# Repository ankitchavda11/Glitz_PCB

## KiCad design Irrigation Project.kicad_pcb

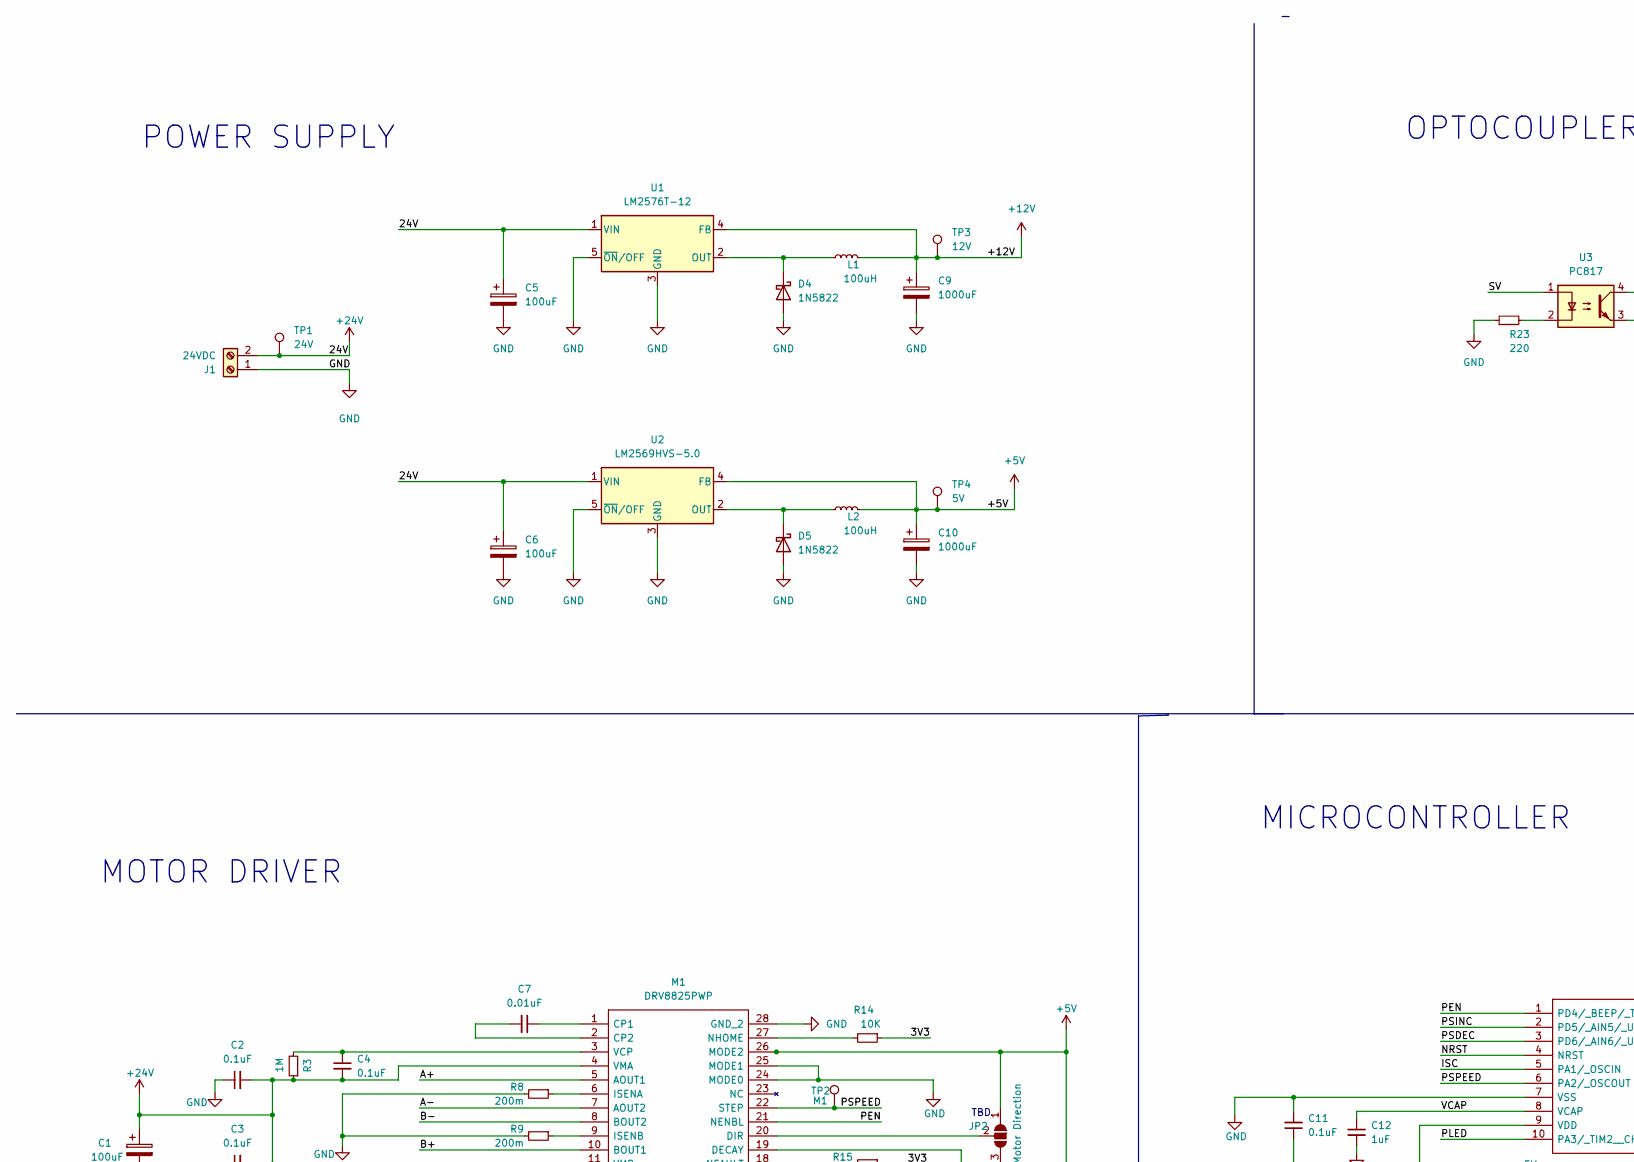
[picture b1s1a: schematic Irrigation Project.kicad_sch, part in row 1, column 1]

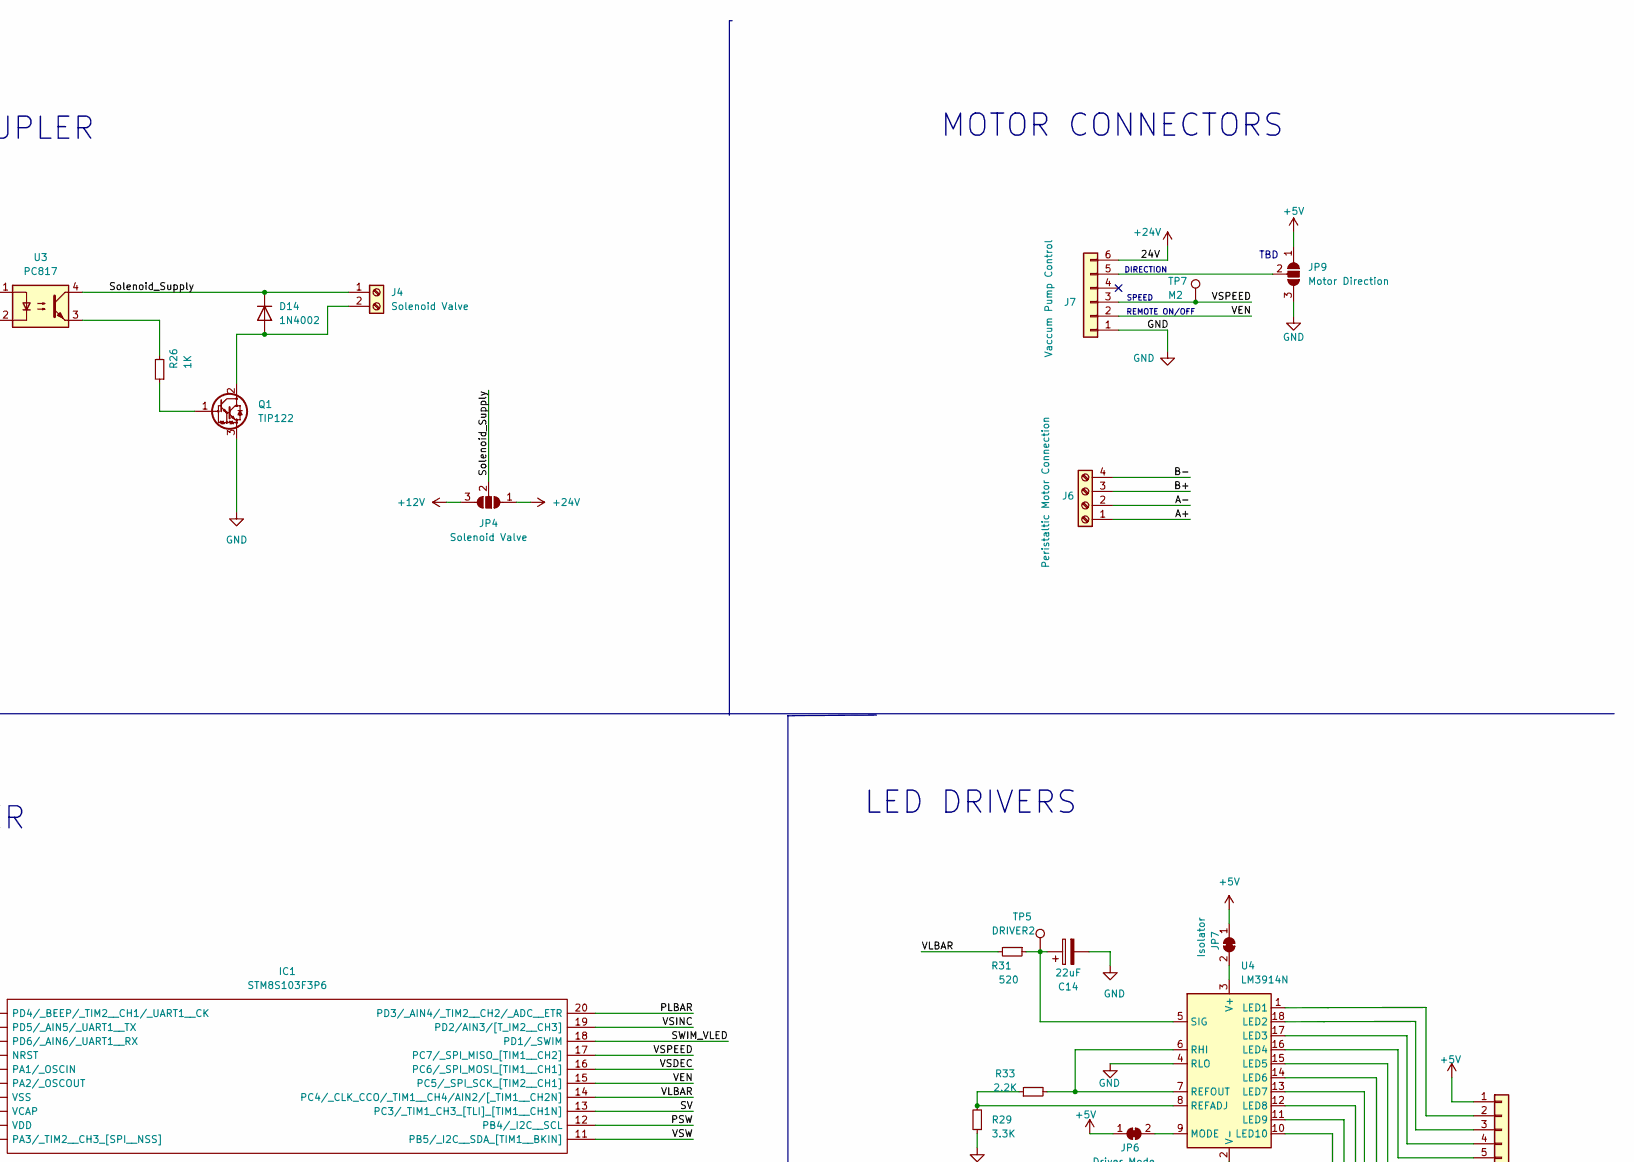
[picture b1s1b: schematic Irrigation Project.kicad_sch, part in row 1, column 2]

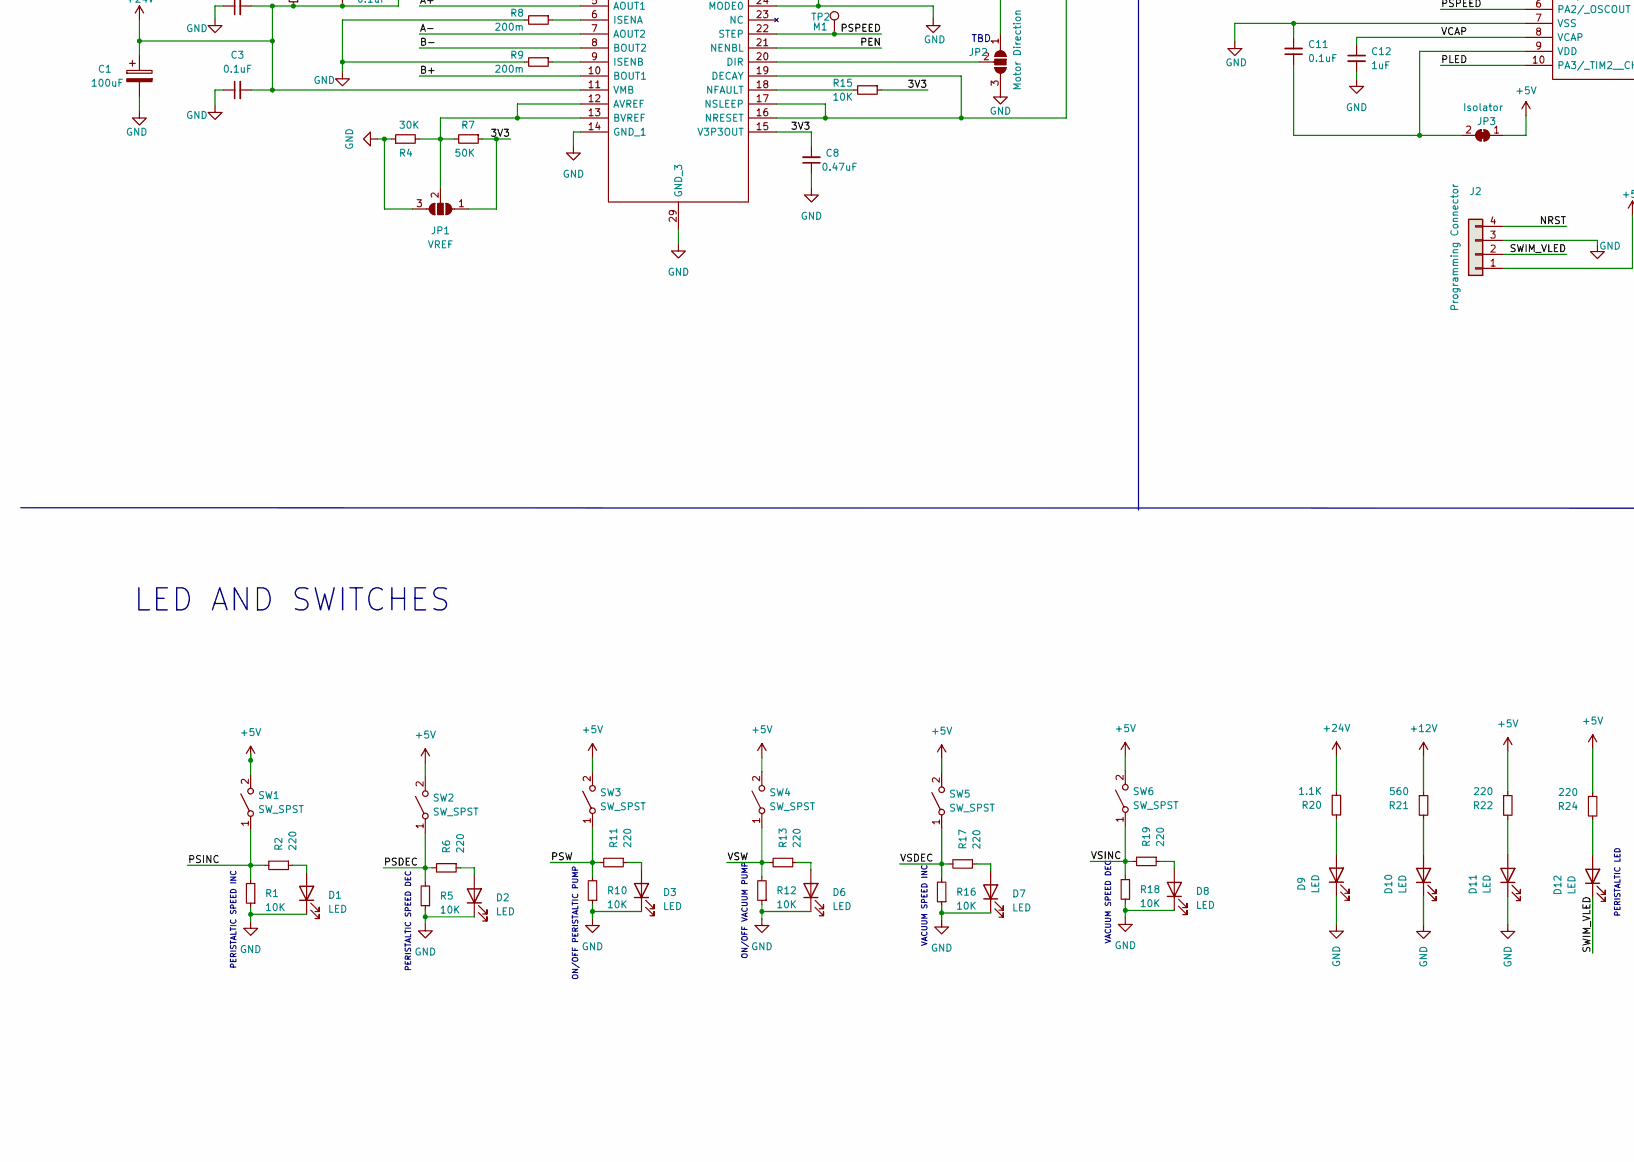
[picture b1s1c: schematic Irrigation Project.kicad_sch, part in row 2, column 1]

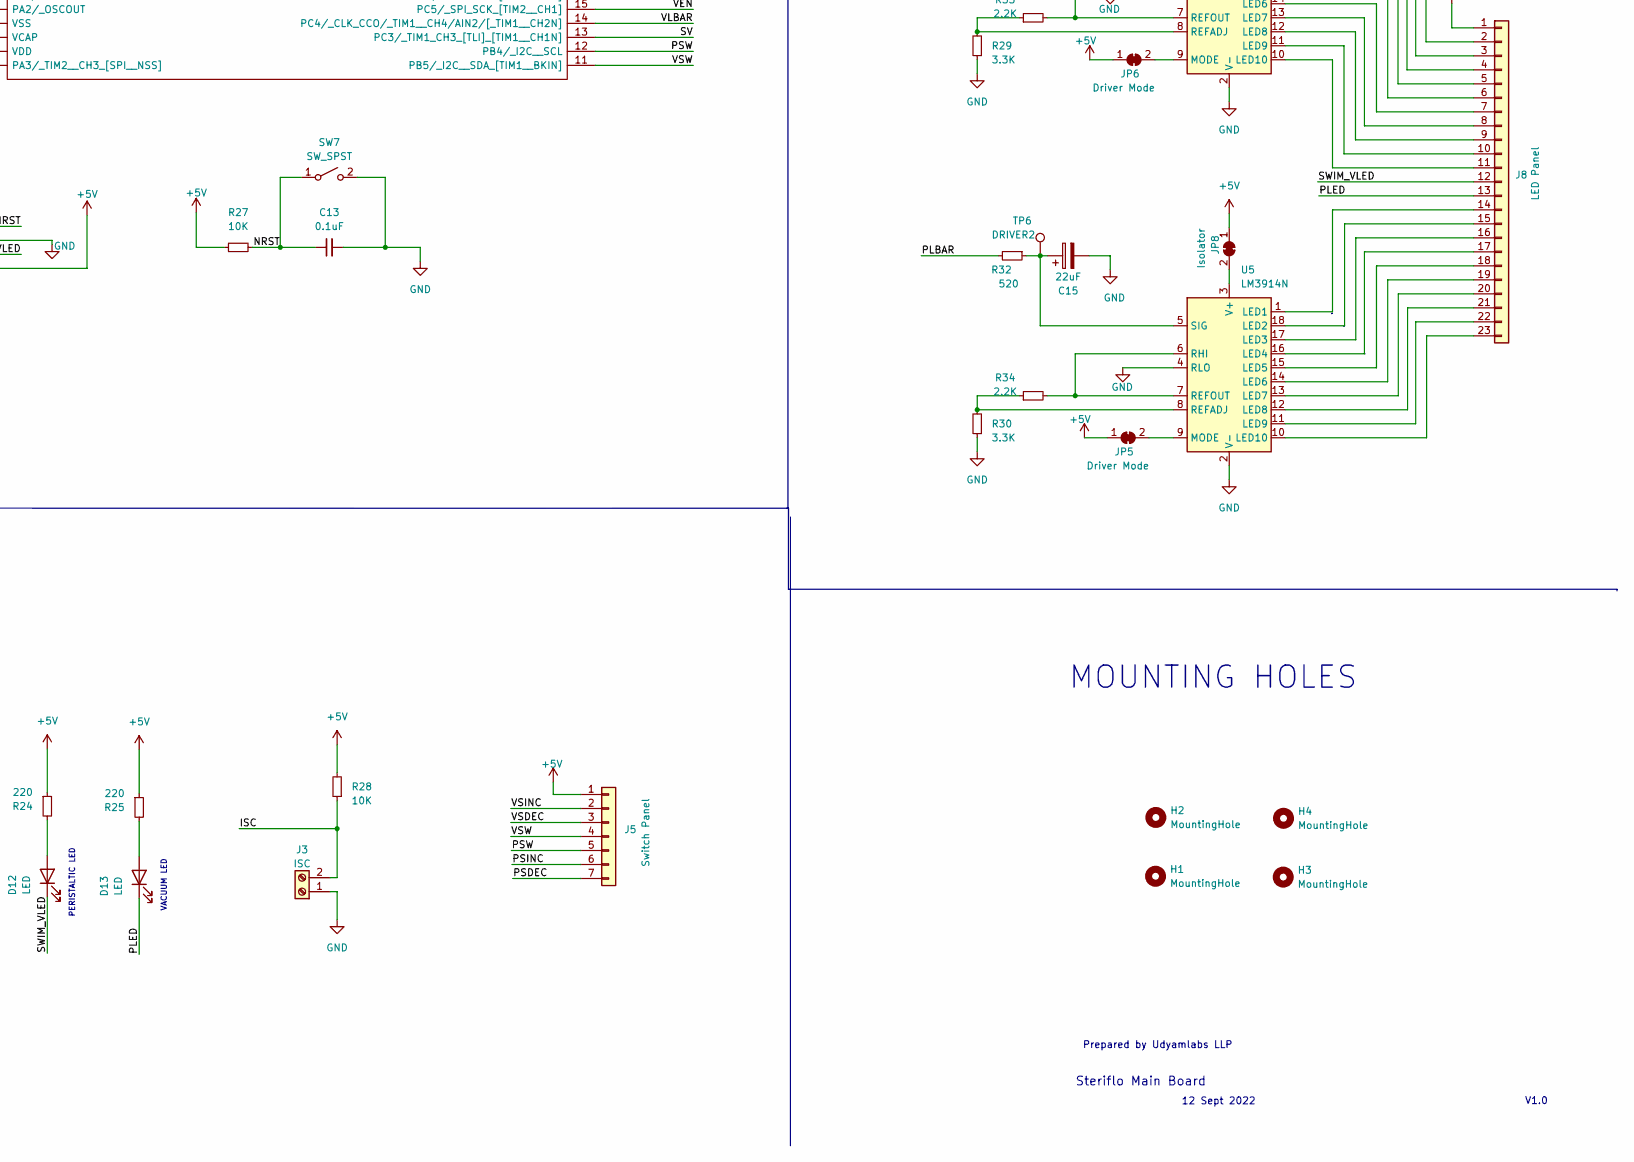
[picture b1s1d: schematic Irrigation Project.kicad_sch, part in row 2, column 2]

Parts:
C1: 100uF; C_1206_3216Metric
C2, C3, C4, C11, C13: 0.1uF; C_0805_2012Metric
C5, C6: 100uF; CP_Elec_6.3x7.7
C7: 0.01uF; C_0805_2012Metric
C8: 0.47uF; C_0805_2012Metric
C9, C10: 1000uF; CP_Radial_D10.0mm_P5.00mm
C12: 1uF; C_0805_2012Metric
C14, C15: 22uF; CP_Radial_D5.0mm_P2.50mm
D1, D2, D3, D6, D7, D8, D9, D10, D11, D12, D13: LED; LED_0805_2012Metric
D4, D5: 1N5822; D_DO-201AD_P15.24mm_Horizontal
D14: 1N4002; D_SMA
H1, H2, H3, H4: MountingHole; MountingHole_3.2mm_M3_ISO7380
IC1: STM8S103F3P6; SOP65P640X120-20N; Manufacturer_Part_Number STM8S103F3P6; Mouser Part Number 511-STM8S103F3P6
J1: 24VDC; PinHeader_1x02_P2.54mm_Vertical
J2: Programming Connector; PinHeader_1x04_P2.54mm_Vertical
J3: ISC; PinHeader_1x02_P2.54mm_Vertical
J4: Solenoid Valve; PinHeader_1x02_P2.54mm_Vertical
J5: Switch Panel; PinHeader_1x07_P2.54mm_Vertical
J6: Peristaltic Motor Connection; TerminalBlock_MetzConnect_Type011_RT05504HBWC_1x04_P5.00mm_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
J7: Vaccum Pump Control; PinHeader_1x06_P2.00mm_Vertical
J8: LED Panel; PinHeader_1x23_P2.54mm_Vertical
JP1: VREF; SolderJumper-3_P1.3mm_Open_Pad1.0x1.5mm
JP2, JP9: Motor Direction; SolderJumper-3_P1.3mm_Open_Pad1.0x1.5mm
JP3, JP7, JP8: Isolator; SolderJumper-2_P1.3mm_Bridged_Pad1.0x1.5mm
JP4: Solenoid Valve; SolderJumper-3_P1.3mm_Bridged12_Pad1.0x1.5mm_NumberLabels
JP5, JP6: Driver Mode; SolderJumper-2_P1.3mm_Bridged_Pad1.0x1.5mm
L1, L2: 100uH; L_Axial_L14.5mm_D5.8mm_P7.62mm_Vertical_Fastron_HBCC
M1: DRV8825PWP; SOP65P640X120-29N; Manufacturer_Part_Number DRV8825PWP; Mouser Part Number 595-DRV8825PWP
Q1: TIP122; TO-220-3_Horizontal_TabDown
R1, R5, R10, R12, R14, R15, R16, R18, R27, R28: 10K; R_0805_2012Metric
R2, R6, R11, R13, R17, R19, R22, R23, R24, R25: 220; R_0805_2012Metric
R3: 1M; R_0805_2012Metric
R4: 30K; R_0805_2012Metric
R7: 50K; R_0805_2012Metric
R8, R9: 200m; R_0805_2012Metric
R20: 1.1K; R_0805_2012Metric
R21: 560; R_0805_2012Metric
R26: 1K; R_0805_2012Metric
R29, R30: 3.3K; R_0805_2012Metric
R31, R32: 520; R_0805_2012Metric
R33, R34: 2.2K; R_0805_2012Metric
SW1, SW2, SW3, SW4, SW5, SW6, SW7: SW_SPST; SW_Push_SPST_NO_Alps_SKRK
TP1: 24V; TestPoint_Pad_2.0x2.0mm
TP2: M1; TestPoint_Pad_2.0x2.0mm
TP3: 12V; TestPoint_Pad_2.0x2.0mm
TP4: 5V; TestPoint_Pad_2.0x2.0mm
TP5, TP6: DRIVER2; TestPoint_Pad_2.0x2.0mm
TP7: M2; TestPoint_Pad_2.0x2.0mm
U1: LM2576T-12; TO-263-5_TabPin3
U2: LM2569HVS-5.0; TO-263-5_TabPin3
U3: PC817; SOT254P975X400-4N
U4, U5: LM3914N; DIP-18_W7.62mm

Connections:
+5V: C10.1, J2.1, J5.1, J8.1, JP2.1 (A), JP3.1 (A), JP5.1 (A), JP6.1 (A), JP7.1 (A), JP8.1 (A), JP9.1 (A), L2.2, M1.16 (NRESET), M1.17 (NSLEEP), M1.19 (DECAY), M1.26 (MODE2), R22.1, R24.1, R25.1, R27.1, R28.2, SW1.2 (B), SW2.2 (B), SW3.2 (B), SW4.2 (B), SW5.2 (B), SW6.2 (B), TP4.1, U2.4 (FB)
+12V: C9.1, JP4.3 (B), L1.2, R21.1, TP3.1, U1.4 (FB)
+24V: C1.1, C2.2, C3.2, C4.2, C5.1, C6.1, J1.2, J7.6, JP4.1 (A), M1.4 (VMA), M1.11 (VMB), R3.1, R20.1, TP1.1, U1.1 (VIN), U2.1 (VIN)
/3V3: C8.2, JP1.1 (A), M1.15 (V3P3OUT), R7.1, R14.1, R15.1
/A+: J6.1, M1.5 (AOUT1)
/A-: J6.2, M1.7 (AOUT2)
/B+: J6.3, M1.10 (BOUT1)
/B-: J6.4, M1.8 (BOUT2)
/ISC: IC1.5 (PA1/_OSCIN), J3.2, R28.1
/NRST: C13.1, IC1.4 (NRST), J2.4, R27.2, SW7.1 (A)
/PEN: IC1.1 (PD4/_BEEP/_TIM2__CH1/_UART1__CK), M1.21 (NENBL)
/PLBAR: IC1.20 (PD3/_AIN4/_TIM2__CH2/_ADC__ETR), R32.2
/PLED: D13.1 (K), IC1.10 (PA3/_TIM2__CH3_[SPI__NSS]), J8.13
/PSDEC: IC1.3 (PD6/_AIN6/_UART1__RX), J5.7, R5.2, R6.2, SW2.1 (A)
/PSINC: IC1.2 (PD5/_AIN5/_UART1__TX), J5.6, R1.2, R2.2, SW1.1 (A)
/PSPEED: IC1.6 (PA2/_OSCOUT), M1.22 (STEP), TP2.1
/PSW: IC1.12 (PB4/_I2C__SCL), J5.5, R10.2, R11.2, SW3.1 (A)
/SV: IC1.13 (PC3/_TIM1_CH3_[TLI]_[TIM1__CH1N]), U3.1
/SWIM_VLED: D12.1 (K), IC1.18 (PD1/_SWIM), J2.2, J8.12
/Solenoid_Supply: D14.1 (K), J4.1, JP4.2 (C), U3.4
/VCAP: C12.1, IC1.8 (VCAP)
/VEN: IC1.15 (PC5/_SPI_SCK_[TIM2__CH1]), J7.2
/VLBAR: IC1.14 (PC4/_CLK_CCO/_TIM1__CH4/AIN2/[_TIM1__CH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), R31.2
/VSDEC: IC1.16 (PC6/_SPI_MOSI_[TIM1__CH1]), J5.3, R16.2, R17.2, SW5.1 (A)
/VSINC: IC1.19 (PD2/AIN3/[T_IM2__CH3]), J5.2, R18.2, R19.2, SW6.1 (A)
/VSPEED: IC1.17 (PC7/_SPI_MISO_[TIM1__CH2]), J7.3, TP7.1
/VSW: IC1.11 (PB5/_I2C__SDA_[TIM1__BKIN]), J5.4, R12.2, R13.2, SW4.1 (A)
GND: C1.2, C2.1, C3.1, C5.2, C6.2, C8.1, C9.2, C10.2, C11.2, C12.2, C13.2, C14.2, C15.2, D1.1 (K), D2.1 (K), D3.1 (K), D4.2 (A), D5.2 (A), D6.1 (K), D7.1 (K), D8.1 (K), D9.1 (K), D10.1 (K), D11.1 (K), IC1.7 (VSS), J1.1, J2.3, J3.1, J7.1, JP1.3 (B), JP2.3 (B), JP9.3 (B), M1.14 (GND_1), M1.24 (MODE0), M1.25 (MODE1), M1.28 (GND_2), M1.29 (GND_3), Q1.3 (E), R1.1, R4.1, R5.1, R8.2, R9.2, R10.1, R12.1, R16.1, R18.1, R23.1, R29.1, R30.1, SW7.2 (B), U1.3 (GND), U1.5 (~ON/OFF), U2.3 (GND), U2.5 (~ON/OFF), U4.2 (V-), U4.4 (RLO), U5.2 (V-), U5.4 (RLO)
unnamed: C4.1, M1.3 (VCP), R3.2
unnamed: C7.1, M1.1 (CP1)
unnamed: C7.2, M1.2 (CP2)
unnamed: C11.1, IC1.9 (VDD), JP3.2 (B)
unnamed: C14.1, R31.1, TP5.1, U4.5 (SIG)
unnamed: C15.1, R32.1, TP6.1, U5.5 (SIG)
unnamed: D1.2 (A), R2.1
unnamed: D2.2 (A), R6.1
unnamed: D3.2 (A), R11.1
unnamed: D4.1 (K), L1.1, U1.2 (OUT)
unnamed: D5.1 (K), L2.1, U2.2 (OUT)
unnamed: D6.2 (A), R13.1
unnamed: D7.2 (A), R17.1
unnamed: D8.2 (A), R19.1
unnamed: D9.2 (A), R20.2
unnamed: D10.2 (A), R21.2
unnamed: D11.2 (A), R22.2
unnamed: D12.2 (A), R24.2
unnamed: D13.2 (A), R25.2
unnamed: D14.2 (A), J4.2, Q1.2 (C)
unnamed: J7.5, JP9.2 (C)
unnamed: J8.2, U4.1 (LED1)
unnamed: J8.3, U4.18 (LED2)
unnamed: J8.4, U4.17 (LED3)
unnamed: J8.5, U4.16 (LED4)
unnamed: J8.6, U4.15 (LED5)
unnamed: J8.7, U4.14 (LED6)
unnamed: J8.8, U4.13 (LED7)
unnamed: J8.9, U4.12 (LED8)
unnamed: J8.10, U4.11 (LED9)
unnamed: J8.11, U4.10 (LED10)
unnamed: J8.14, U5.1 (LED1)
unnamed: J8.15, U5.18 (LED2)
unnamed: J8.16, U5.17 (LED3)
unnamed: J8.17, U5.16 (LED4)
unnamed: J8.18, U5.15 (LED5)
unnamed: J8.19, U5.14 (LED6)
unnamed: J8.20, U5.13 (LED7)
unnamed: J8.21, U5.12 (LED8)
unnamed: J8.22, U5.11 (LED9)
unnamed: J8.23, U5.10 (LED10)
unnamed: JP1.2 (C), M1.12 (AVREF), M1.13 (BVREF), R4.2, R7.2
unnamed: JP2.2 (C), M1.20 (DIR)
unnamed: JP5.2 (B), U5.9 (MODE)
unnamed: JP6.2 (B), U4.9 (MODE)
unnamed: JP7.2 (B), U4.3 (V+)
unnamed: JP8.2 (B), U5.3 (V+)
unnamed: M1.6 (ISENA), R8.1
unnamed: M1.9 (ISENB), R9.1
unnamed: M1.18 (NFAULT), R15.2
unnamed: M1.27 (NHOME), R14.2
unnamed: Q1.1 (B), R26.1
unnamed: R23.2, U3.2
unnamed: R26.2, U3.3
unnamed: R29.2, R33.1, U4.8 (REFADJ)
unnamed: R30.2, R34.1, U5.8 (REFADJ)
unnamed: R33.2, U4.6 (RHI), U4.7 (REFOUT)
unnamed: R34.2, U5.6 (RHI), U5.7 (REFOUT)

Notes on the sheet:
POWER SUPPLY
VACUUM LED
ON/OFF PERISTALTIC PUMP
MICROCONTROLLER
LED AND SWITCHES
ON/OFF VACUUM PUMP
12 Sept 2022
PERISTALTIC SPEED INC
Prepared by Udyamlabs LLP
Steriflo Main Board
TBD
PERISTALTIC SPEED DEC
MOUNTING HOLES
REMOTE ON/OFF
PERISTALTIC LED
VACUUM SPEED DEC
MOTOR DRIVER
V1.0
VACUUM SPEED INC
OPTOCOUPLER
LED DRIVERS
SPEED
MOTOR CONNECTORS
DIRECTION

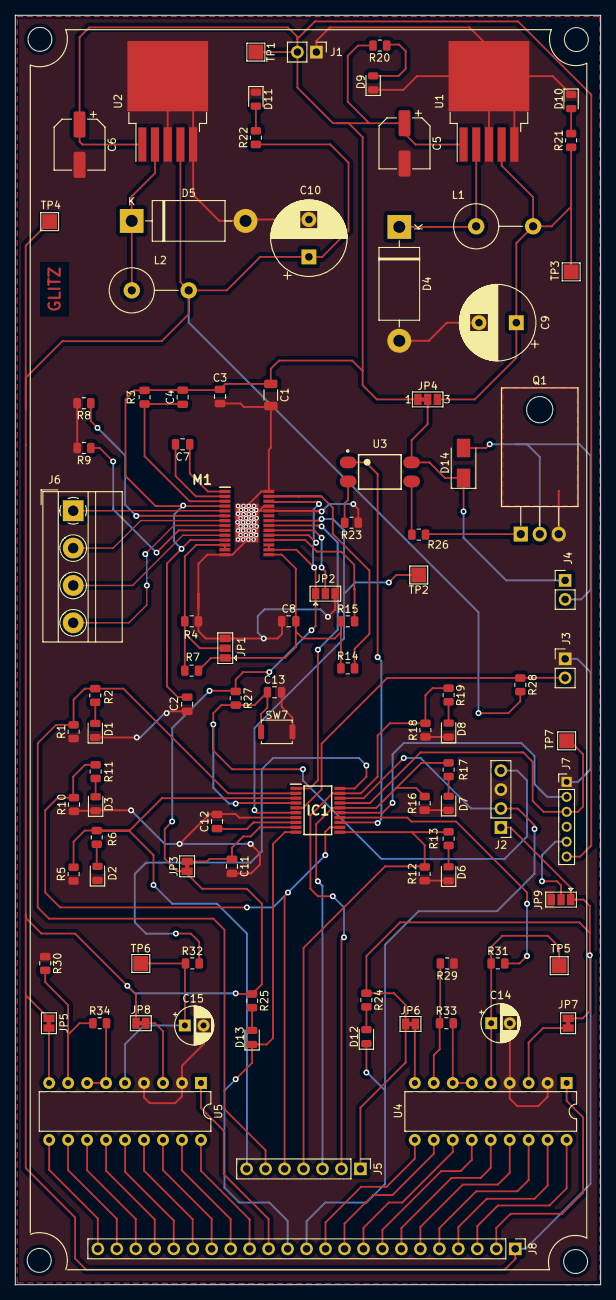
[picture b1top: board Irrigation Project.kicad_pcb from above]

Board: 2 copper layers, 78.3 x 169.9 mm, 102 parts (0 on the bottom side), 86 nets.

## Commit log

2022-09-18 PCB_design
